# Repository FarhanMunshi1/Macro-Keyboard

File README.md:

The schematics, PCB design, and test code to make a macro keyboard.
Software used : Arduino, KiCad

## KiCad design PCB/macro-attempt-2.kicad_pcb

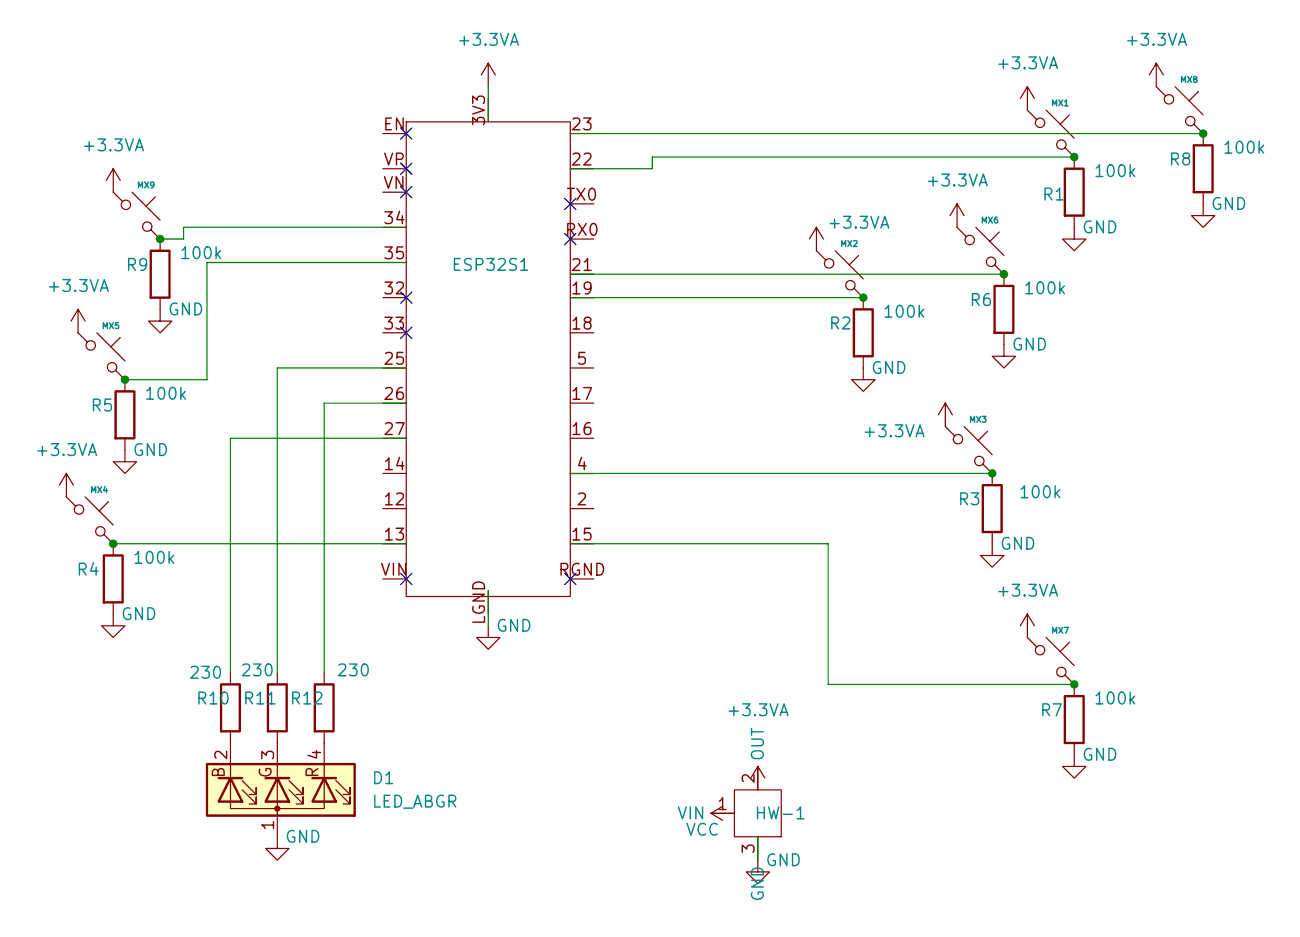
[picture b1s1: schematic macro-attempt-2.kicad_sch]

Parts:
D1: LED_ABGR; LED_D5.0mm-4_RGB_Staggered_Pins
ESP32S1: ESP32-WROOM-32
HW-1: HW-764
MX1, MX2, MX3, MX4, MX5, MX6, MX7, MX8, MX9: MX_SW_solder; SW_MX_1u_NOSUPPORT
R1, R2, R3, R4, R5, R6, R7, R8, R9: 100k; R_Axial_DIN0207_L6.3mm_D2.5mm_P10.16mm_Horizontal
R10, R11, R12: 230; R_Axial_DIN0207_L6.3mm_D2.5mm_P10.16mm_Horizontal

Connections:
+3.3VA: ESP32S1.3V3, HW-1.2 (OUT), MX1.1, MX2.1, MX3.1, MX4.1, MX5.1, MX6.1, MX7.1, MX8.1, MX9.1
GND: D1.1 (A), ESP32S1.LGND, HW-1.3 (GND), R1.2, R2.2, R3.2, R4.2, R5.2, R6.2, R7.2, R8.2, R9.2
unnamed 2: D1.2 (BK), R10.2; also elsewhere on the board
unnamed 3: D1.3 (GK), R11.2; also elsewhere on the board
unnamed: D1.4 (RK), R12.2
unnamed: ESP32S1.4, MX3.2, R3.1
unnamed: ESP32S1.13, MX4.2, R4.1
unnamed: ESP32S1.15, MX7.2, R7.1
unnamed: ESP32S1.19, MX2.2, R2.1
unnamed: ESP32S1.21, MX6.2, R6.1
unnamed: ESP32S1.22, MX1.2, R1.1
unnamed: ESP32S1.23, MX8.2, R8.1
unnamed 12: ESP32S1.25, R11.1; also elsewhere on the board
unnamed: ESP32S1.26, R12.1
unnamed 14: ESP32S1.27, R10.1; also elsewhere on the board
unnamed: ESP32S1.34, MX9.2, R9.1
unnamed: ESP32S1.35, MX5.2, R5.1
VCC: HW-1.1 (VIN)

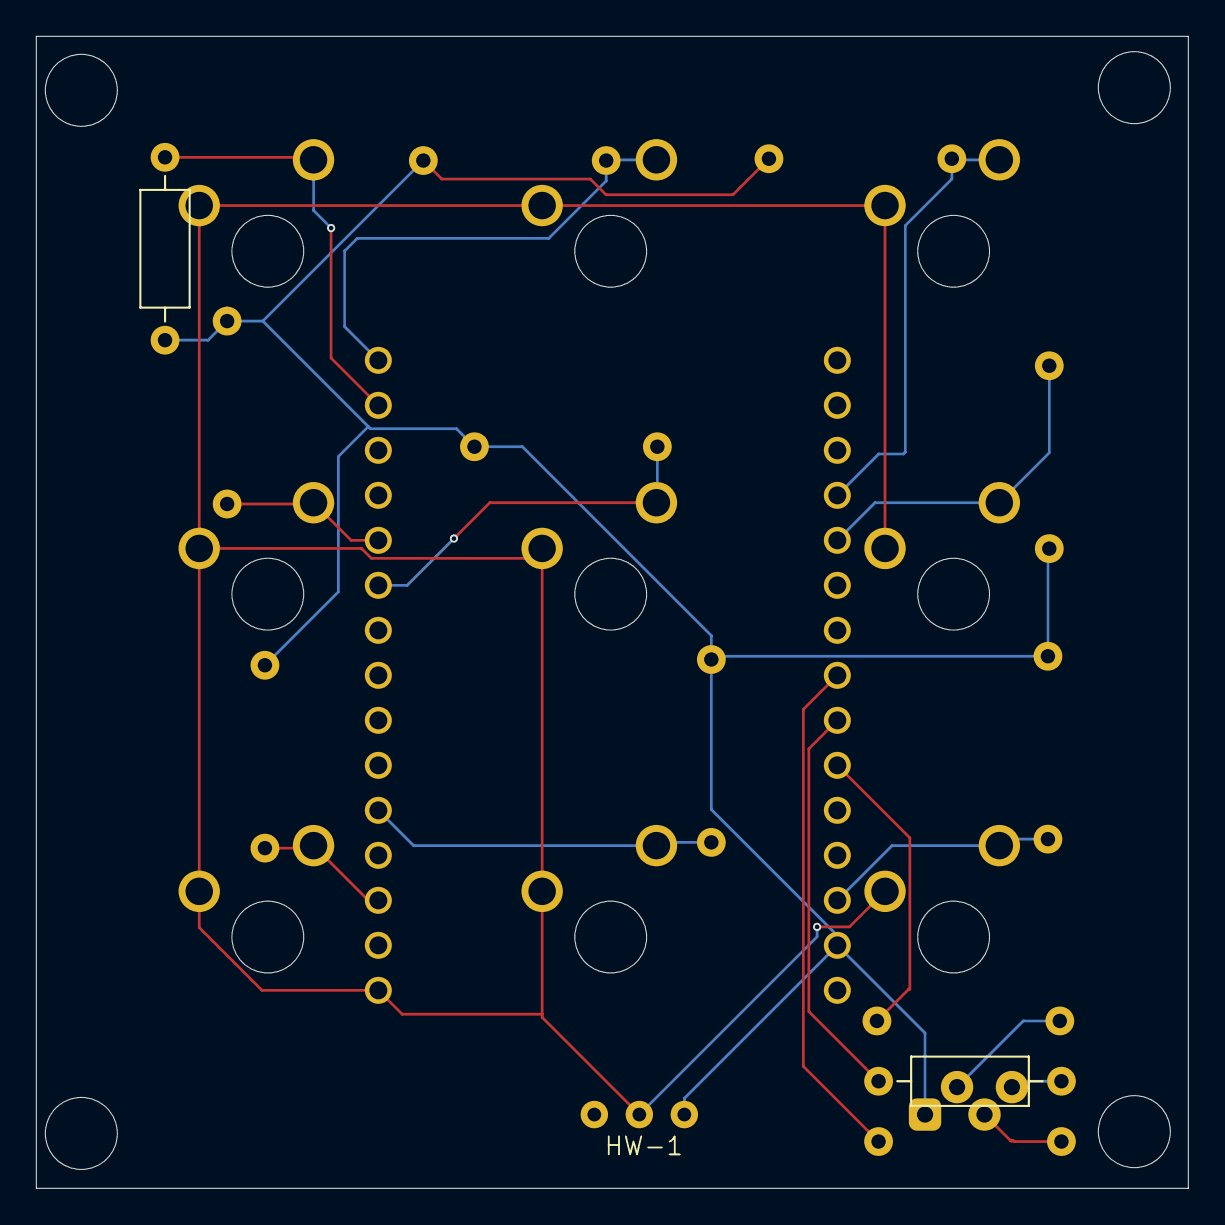
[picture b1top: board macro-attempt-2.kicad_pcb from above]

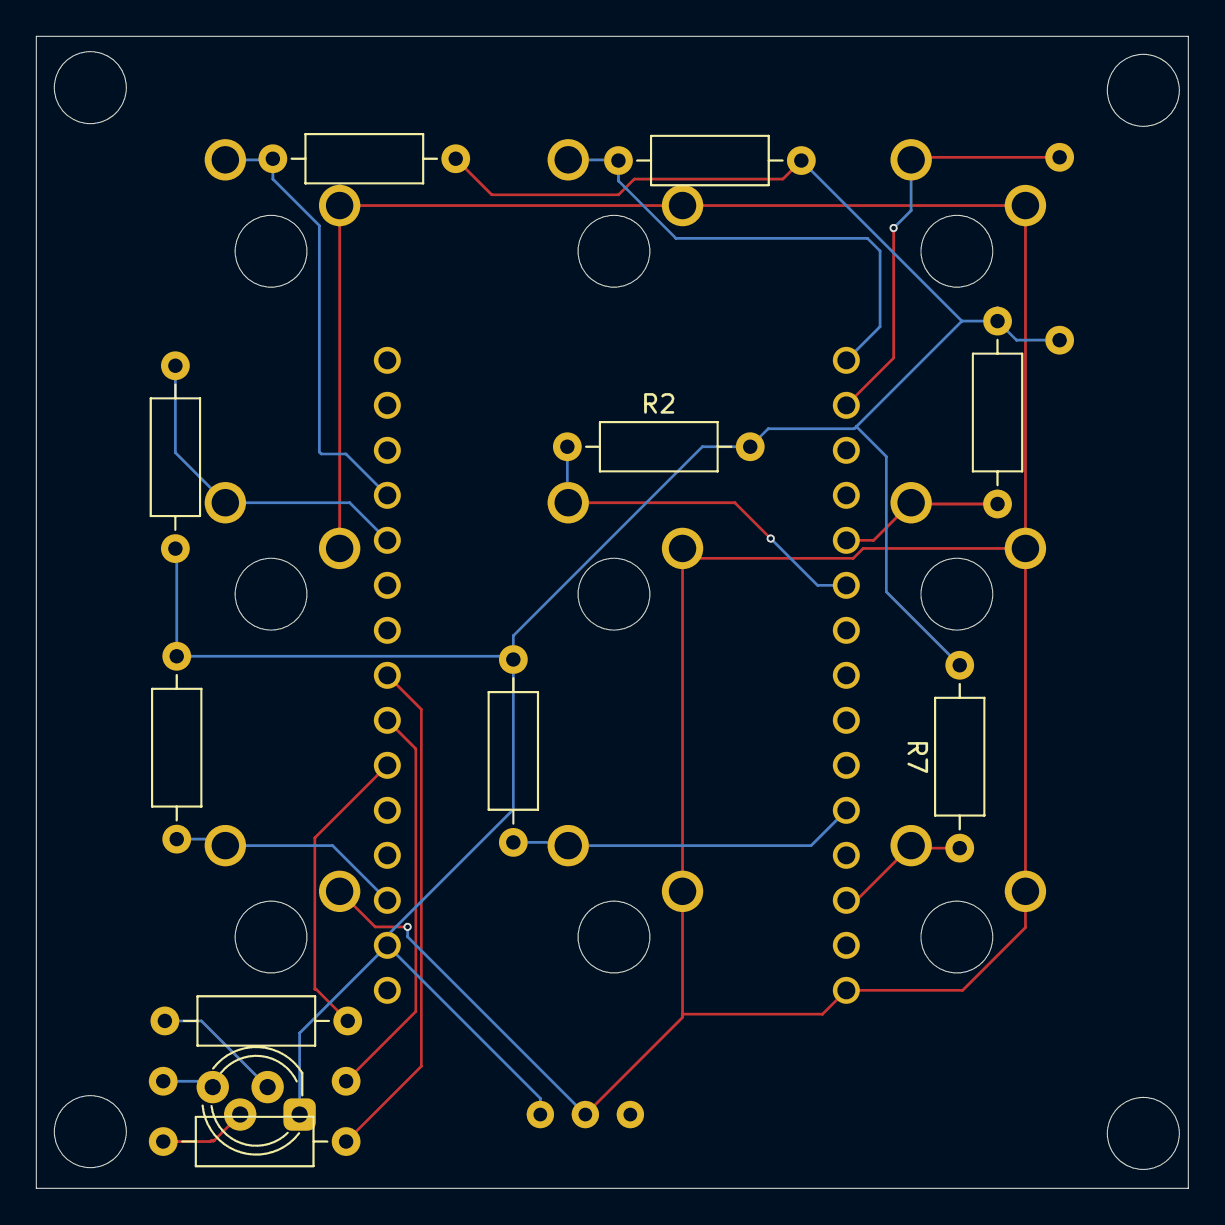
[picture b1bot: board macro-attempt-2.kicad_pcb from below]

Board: 2 copper layers, 64.0 x 64.0 mm, 24 parts (12 on the bottom side), 17 nets.

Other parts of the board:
LED_R: 230; R_Axial_DIN0207_L6.3mm_D2.5mm_P10.16mm_Horizontal
LED_R#2: 230; R_Axial_DIN0207_L6.3mm_D2.5mm_P10.16mm_Horizontal

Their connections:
unnamed 2: LED_R.2; also elsewhere on the board
unnamed 3: LED_R#2.2; also elsewhere on the board
unnamed 12: LED_R#2.1; also elsewhere on the board
unnamed 14: LED_R.1; also elsewhere on the board

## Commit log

2025-04-03 initial
2025-07-02 savepoint
